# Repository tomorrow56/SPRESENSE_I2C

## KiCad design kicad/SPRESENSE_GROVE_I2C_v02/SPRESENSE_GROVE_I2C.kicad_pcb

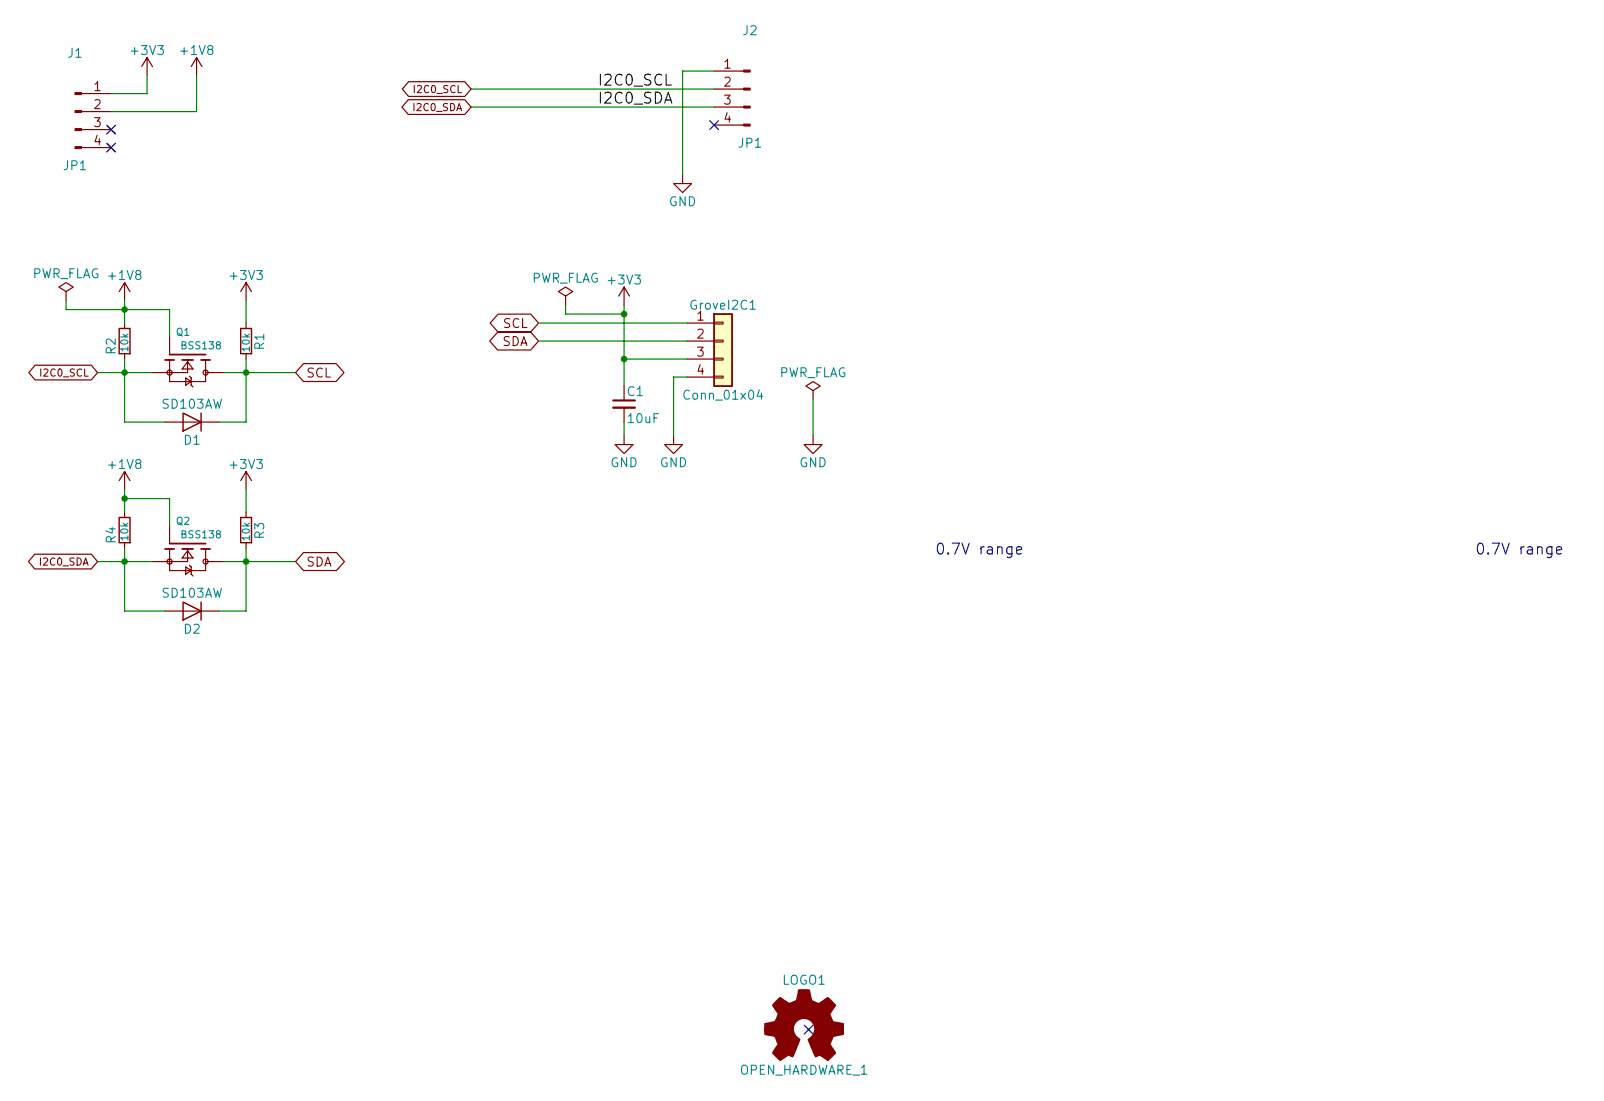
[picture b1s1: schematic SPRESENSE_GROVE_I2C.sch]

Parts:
C1: 10uF; C_0603
D1, D2: SD103AW; D_SOD-123
GroveI2C1: Conn_01x04; Grove_4x2.00mm_Angle
J1, J2: JP1; Pin_Header_Straight_1x04_Pitch2.54mm
LOGO1: OPEN_HARDWARE_1; OSHW-logo_silkscreen-front_2mm
Q1, Q2: BSS138; SOT-23
R1, R2, R3, R4: 10k; R_0603

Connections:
+1V8: J1.2, Q1.1 (G), Q2.1 (G), R2.2, R4.2
+3V3: C1.1, GroveI2C1.3, J1.1, R1.2, R3.2; also elsewhere on the board
GND: C1.2, GroveI2C1.4, J2.1; also elsewhere on the board
I2C0_SCL: D1.2 (A), J2.2, Q1.2 (S), R2.1
I2C0_SDA: D2.2 (A), J2.3, Q2.2 (S), R4.1
SCL: D1.1 (K), GroveI2C1.1, Q1.3 (D), R1.1; also elsewhere on the board
SDA: D2.1 (K), GroveI2C1.2, Q2.3 (D), R3.1; also elsewhere on the board

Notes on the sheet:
0.7V range

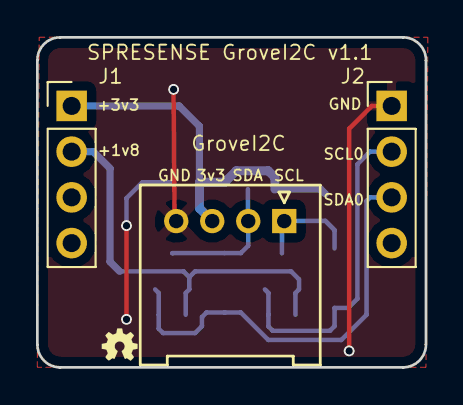
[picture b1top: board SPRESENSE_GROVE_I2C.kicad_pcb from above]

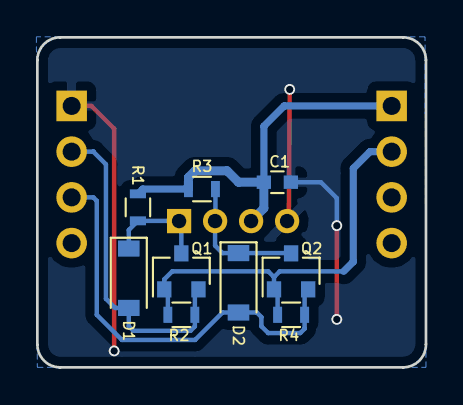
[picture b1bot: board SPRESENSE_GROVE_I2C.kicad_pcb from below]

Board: 2 copper layers, 21.6 x 18.3 mm, 13 parts (9 on the bottom side), 7 nets.

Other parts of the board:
GroveI2C: Conn_01x04; Grove_4x2.00mm_Angle

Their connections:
+3V3: GroveI2C.3; also elsewhere on the board
GND: GroveI2C.4; also elsewhere on the board
SCL: GroveI2C.1; also elsewhere on the board
SDA: GroveI2C.2; also elsewhere on the board

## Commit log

2020-01-21 add schematics
2020-01-21 add sample sketch and kicad data
